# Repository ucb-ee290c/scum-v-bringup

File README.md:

# scum-v-bringup

Various files for bringing up the Single-Chip Micro Mote V (SCμM-V)

## Documentation

📖 **[SCuM-V Documentation (Nextra Site)](https://ucb-ee290c.github.io/scum-v-bringup/)** - Interactive documentation

### Contributing to Documentation
- **Nextra Documentation**: Edit files in `docs/` and submit pull requests
- **Legacy AsciiDoc**: See [Contributing to the specification document](docs/README.md)

### Installing Node.js and npm

npm is bundled with Node.js. Install Node.js for your OS, then verify with `node -v` and `npm -v`.

- **Windows**:
  - Download the LTS installer from the [official Node.js download page](https://nodejs.org/en/download/)
  - Run the `.msi` and follow the prompts
  - Verify: `node -v` and `npm -v`

- **macOS**:
  - Install Homebrew (if not installed):
    ```bash
    /bin/bash -c "$(curl -fsSL https://raw.githubusercontent.com/Homebrew/install/HEAD/install.sh)"
    ```
  - Install Node.js (includes npm):
    ```bash
    brew install node
    ```
  - Verify: `node -v` and `npm -v`

- **Linux (Ubuntu/Debian)**:
  - Update and install:
    ```bash
    sudo apt update
    sudo apt install nodejs npm
    ```
  - Verify: `node -v` and `npm -v`

- **More options**: See the official npm guide: [Downloading and installing Node.js and npm](https://docs.npmjs.com/downloading-and-installing-node-js-and-npm)

#### How to contribute to the docs
1. Fork the repo on GitHub: [ucb-ee290c/scum-v-bringup](https://github.com/ucb-ee290c/scum-v-bringup)
2. Clone your fork:
   ```bash
   git clone https://github.com/<your-username>/scum-v-bringup.git
   cd scum-v-bringup
   ```
3. Create a branch:
   ```bash
   git checkout -b docs/your-change
   ```
4. Edit files under `docs/`, preview locally (below), commit and push:
   ```bash
   git add .
   git commit -m "docs: describe your change"
   git push origin docs/your-change
   ```
5. Open a Pull Request to `ucb-ee290c/scum-v-bringup` with a clear description.

### Building Documentation Locally
```bash
cd docs
npm install
npm run dev    # Development server at http://localhost:3000
npm run build  # Production build
```

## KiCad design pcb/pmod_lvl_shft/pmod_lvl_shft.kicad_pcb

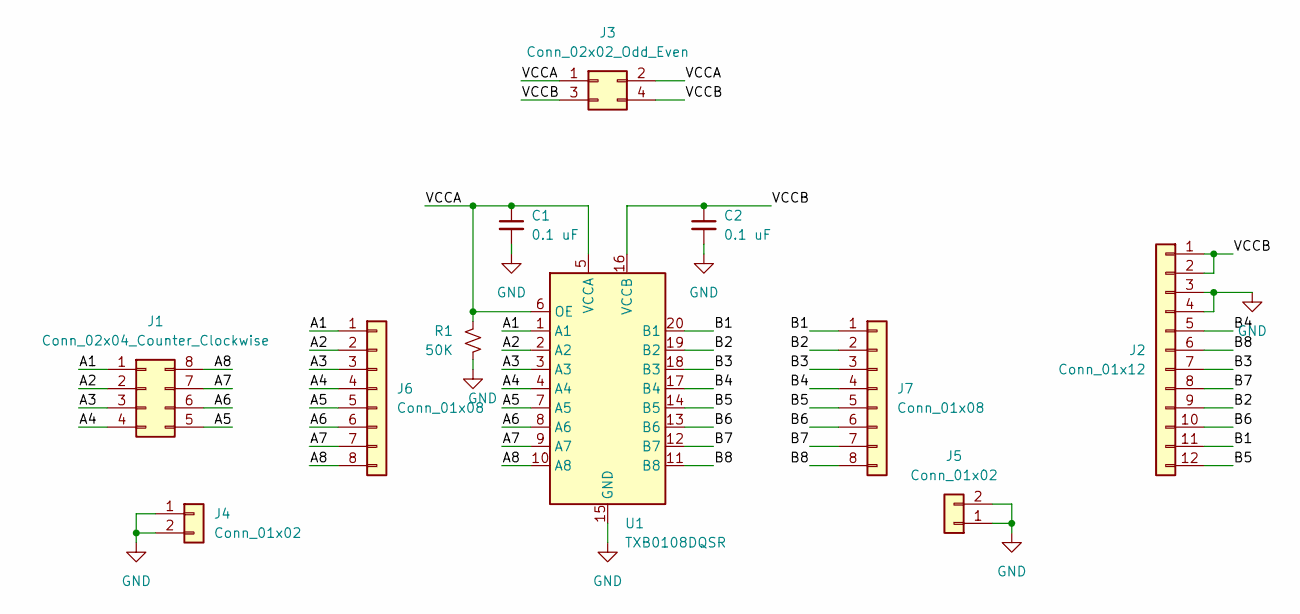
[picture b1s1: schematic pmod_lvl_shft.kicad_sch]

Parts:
C1, C2: 0.1 uF; C_0603_1608Metric
J1: Conn_02x04_Counter_Clockwise; PinHeader_2x04_P2.54mm_Vertical
J2: Conn_01x12; PinHeader_2x06_P2.54mm_Horizontal
J3: Conn_02x02_Odd_Even; PinHeader_2x02_P2.54mm_Vertical
J4, J5: Conn_01x02; PinHeader_1x02_P2.54mm_Vertical
J6, J7: Conn_01x08; PinHeader_1x08_P2.54mm_Vertical
R1: 50K; R_0603_1608Metric
U1: TXB0108DQSR; USON-20_2x4mm_P0.4mm

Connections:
/A1: J1.1, J6.1, U1.1 (A1)
/A2: J1.2, J6.2, U1.2 (A2)
/A3: J1.3, J6.3, U1.3 (A3)
/A4: J1.4, J6.4, U1.4 (A4)
/A5: J1.5, J6.5, U1.7 (A5)
/A6: J1.6, J6.6, U1.8 (A6)
/A7: J1.7, J6.7, U1.9 (A7)
/A8: J1.8, J6.8, U1.10 (A8)
/B1: J2.11, J7.1, U1.20 (B1)
/B2: J2.9, J7.2, U1.19 (B2)
/B3: J2.7, J7.3, U1.18 (B3)
/B4: J2.5, J7.4, U1.17 (B4)
/B5: J2.12, J7.5, U1.14 (B5)
/B6: J2.10, J7.6, U1.13 (B6)
/B7: J2.8, J7.7, U1.12 (B7)
/B8: J2.6, J7.8, U1.11 (B8)
/VCCA: C1.1, J3.1, J3.2, R1.1, U1.5 (VCCA), U1.6 (OE)
/VCCB: C2.1, J2.1, J2.2, J3.3, J3.4, U1.16 (VCCB)
GND: C1.2, C2.2, J2.3, J2.4, J4.1, J4.2, J5.1, J5.2, R1.2, U1.15 (GND)

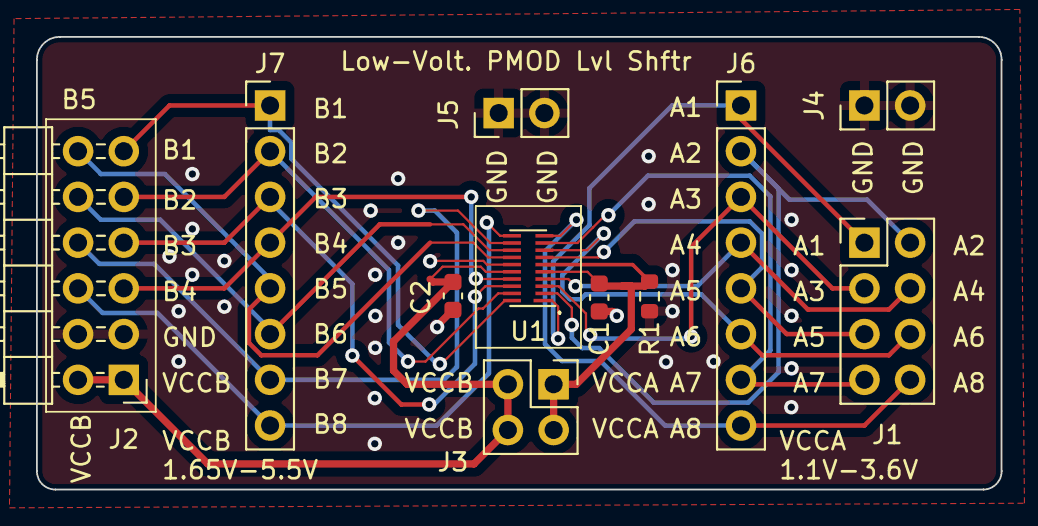
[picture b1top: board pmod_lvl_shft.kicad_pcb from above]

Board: 2 copper layers, 53.6 x 25.1 mm, 11 parts (0 on the bottom side), 19 nets.

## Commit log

2022-12-06 init
2022-12-06 add scan chain wip
2023-01-05 simulation verified UART<->scan chain bridge
2023-01-05 readme
2023-02-07 SCAN_CLK_FREQ fixed, set to 1 kHz, redefined UART response
2023-02-07 Added wip Python client to communicate with FPGA
2023-02-07 Vivado proj tcl (build.tcl), .gitignore, and build checkpoint
2023-02-11 ASC client packets to bypass on-chip clocks
2023-02-11 More README documentation on hardware setup
2023-02-11 Abstractions of scan chain payloads
2023-02-11 FPGA setup and bitstream generation documentation
2023-02-11 Fixes to and renaming of build.tcl -> create_project.tcl
2023-02-11 Added README section on writing to the ASC
2023-02-12 Add ability to use button 0 for chip reset
2023-02-19 add scanchain payload class and analog_rf payload
2023-02-19 Added scum_firmware
2023-02-19 Simple hello world firmware + fixes
2023-02-19 Added tl_host.py
2023-02-19 Added TileLinkTrafficAdapter-F446
2023-02-26 Adding documentation on the TSI setup with STM32
2023-02-26 Added tiny_adapter and proxyFESVR fork
2023-02-26 Added project structure to README
2023-02-26 ASC bitstream flashing guide and Tcl script fix/guide
2023-02-26 Remove sim_compile_state
2023-03-21 Working scum-v bootload
    64-bit oriented TSI interface uploads 8 bytes to SRAM at a time in double-word aligned addressing
2023-04-08 Added code from FPU experiments
2023-04-08 Cleanup of scan chain client.py
2023-04-26 Implemented SCuM-V22 baseband C library
2023-04-26 SRAM poke to verify bootload completion
2023-04-26 ADC clock tuning in the scan chain
2023-04-26 Include baseband library in Makefile
2023-04-26 Added BLE and LRWPAN loopback tests
2023-04-26 scum_firmware setup for dynamic power consumption test
2023-04-26 ARCH and ABI compiler flags for SCuM-V23
2023-04-28 Add oscibear rx sim
2023-05-23 Added MMCM clock generation wizard
2023-05-23 Added 200 kHz and 20 MHz generated CPU clocks
2023-08-18 scumv-23 spec doc, asciidoc setup & guide
2023-08-18 Create publish.yml GH action
2023-08-18 Handle vscode vs gh actions envs for spec doc
2023-08-18 More spec doc substance
2023-08-18 Power system and uv-adc specs
2023-08-22 Documenting the digital core
2023-08-22 Rename ebook.pdf to SCuM-V23.pdf
2023-08-22 Add links to the documentation
2023-08-22 Use SCuM-V23.pdf link
2023-08-22 Add workarounds around asciidoctor ghpages action
2023-08-23 More documentation throughout
2023-08-24 added RF Analog section
2023-08-24 Include radio.adoc in scum-v23.adoc
2023-08-29 Change radar to radar transmitter
2023-08-31 Update SCuM-V23.adoc
    Names on tasks
2023-08-31 Add designer, author, and bringup names
2023-08-31 Format names
2023-08-31 Update SCuM-V23.adoc
    point final review slides to bringup drive
2023-08-31 point final review to bringup drive
2023-09-01 Revert "Format names"
    This reverts commit 35be374bae99f2b7b4f217b85905e1dc431e396a.
2023-09-01 Revert "Add designer, author, and bringup names"
    This reverts commit bd3a76473c84f6a26f82226a87aa97f5dfc6dda7.
2023-09-02 Fix google slides links
2023-09-02 Edit DRI names for documentation
2023-09-02 Add radar documentation
2023-09-02 Convert PDF images to PNG images
2023-09-02 Add radar layout
2023-09-02 Add documentation for radio transmitter
2023-09-05 Add files for encryption modules documentation
2023-09-05 Add base address for Scumvtuning
2023-10-05 Format register table for radars
2023-10-05 Update ramp generator clock mux select
2023-12-03 tl_host for 32-bit targets
2023-12-06 Change V22 to V23
2023-12-06 Fix UART base address in scum.h
2023-12-06 Use different baudrate, worked with 200 kHz
2023-12-08 Read 16 bytes from serial
2023-12-08 Lint tl_host.py
2023-12-08 Add TileLink adapter firmware for STM32H723ZGT6
2023-12-08 Change MISO -> OUT and MOSI -> IN in H723 firmware
2023-12-09 Change from 64-bit data to 32-bit data
2023-12-13 Revert "Change from 64-bit data to 32-bit data"
    This reverts commit 6d54f9f602f0e73b2d929a87955d22fd9ce4ed78.
2023-12-17 Update scum_firmware source from scum-sim-par
2023-12-17 Added scripts/smartelf2hex.sh
2023-12-17 Add template project
2023-12-17 Poll TL_CLK instead of an interrupt
2023-12-19 Increase CPU clock to 500 MHz / HCLK to 250 MHz
2023-12-19 Poll TL_CLK instead of an interrupt (#4)
    * Poll TL_CLK instead of an interrupt
    * Increase CPU clock to 500 MHz / HCLK to 250 MHz
2023-12-19 Clean up TL host script
2023-12-19 Add information about STM32H723ZG to README.md
2024-01-05 Add sensor_adc python test script
2024-01-08 Clarify base address of uv-adc in docs
2024-01-08 Add example usage doc to sensor_adc.py
2024-01-09 sensor_adc.py more comprehensive test script, option for bootload, better config function
2024-01-09 Added sensor_adc signal processing scripts; mainly SENSOR_OUT related
    Associated raw data (csv)
    https://berkeley.box.com/s/r1d8qseaqz2fsj55ihhmtkpoj31uxdyu
2024-01-22 Add sensor_adc_test firmware
2024-01-30 Remove scanchain.gen files
2024-01-30 Update the README.md with how to create the Vivado project
2024-02-02 Remove clock generation from FPGA
2024-02-02 Ignore steps to reproduce files
2024-02-02 Clean up FPGA client script
2024-02-02 Add SCuM-V23 scanchain Verilog file
2024-02-03 Update FPGA code and client script to match SCuM-V23's scan chain
2024-02-05 WIP BLE & 15.4 loopback firmware changes
2024-02-05 sensor_adc_test firmware with log_counters data collection
2024-02-05 Scan chain VCO LO tuning/characterization script
2024-02-08 Fix typo in client.py
2024-02-09 Fix order of oscillator scan chain registers
2024-02-22 Updated more sensor ADC test firmware
2024-02-22 Add plotting scripts and logs for ADC counter tests
2024-03-05 4 instructions per sensor_adc_test logging cycle
2024-03-06 comment out kick IDAC to start up, and set default idac val to be 16
2024-03-10 Sensor ADC tests at 100M/25M CPU/ADC
2024-03-10 Added parse_counter_logs script and data for other CPU/ADC ratios
2024-04-24 Updated parse_counter_logs
2024-05-23 Work in progress sensoradc-bringup FPGA code
2024-05-23 Pruning and bufg clock buffers for ADC_CLOCK
2024-05-23 sensoradc-bringup clock_gen, dechopper, sensor_out_fsm
2024-05-23 Constraints tweak, track design checkpoint
2024-05-23 WIP scumv22 scanchain redux
2024-05-27 create_project.tcl -> make_proj.tcl
2024-05-27 sensoradc-bringup FPGA updated constraints and design checkpoint
2024-05-28 Remove CPU_CLK preventing scan chain synth
2024-05-28 More progress on sensoradc-bringup
2024-05-29 sensoradc-bringup data_translator, uart connection, timing closure
2024-05-29 Fix bugs in a7top
2024-05-29 Add uart_decode.py
2024-05-30 Latest verilog and python
2024-07-16 Successful SCuM-V23B boot
    Working boot with python tl_host --target power_test
2024-07-16 ble_loopback revisions, alignment with scum-v24, not working
2024-07-30 Update README.md with xpack toolchain
2024-07-31 Add sysverilog-source files for R=32,000
2024-07-31 fix: update verilog modules to match sysverilog modules
2024-07-31 Remove unneeded, unused files
2024-07-31 fix: update Verilog modules to match SystemVerilog definitions and fix syntax issues
2024-08-01 feat: reimplement decimator_tb for compatibility with Xilinx Vivado by replacing integer with reg arrays
2024-08-01 Several fixes to comb, dsp_clock_domain_wrapper, integrators for R=32,000 update
2024-08-01 Add PMOD level shfiter PCB
2024-08-01 Build .adoc Files for GitHub Pages from 93667d8c255ccafe95bf72764eb72e34916c16d5
2024-08-01 Docs update for scum-v24
2024-09-07 sensor_adc_test demo with delayed startup, clock divider synchronization
    To eliminate delay between chopper clock edges, for test
2024-09-07 Changes for successful testing session
    Still having harmonics issues
2025-07-27 Copy over scum-test-tools BSP from scumv25 repo
2025-07-27 Copy lib/htif from scum-test-tools scumv25
2025-07-27 scum-test-tools scumv25 startup.S, Makefile, firmware.map
2025-07-27 Copy scum-test-tools core/src from scumv25
2025-07-28 Working compilation for scumv25 (rv64 & new MMIO map)
2025-07-29 Make necessary changed for rv64 -> rv32 for scumv24b
2025-07-29 Correct scumv24 baseband int map
    Source diagram made
2025-07-30 Single TL packet working SCuM-V24B
2025-07-30 Seemingly working single-shot TL transactions
2025-07-31 Initial implementation of scumv-controller FPGA SerialTL
2025-07-31 Somewhat working UART<->TL traffic adapter
2025-08-04 scumv-controller add IO pins to XDC for TL bus
2025-08-04 Revisions to scumv-controller FSMs per benchtop debugging with ILA
2025-08-05 Working scumv-controller single TL sends on bench
2025-08-05 Improved scumv-controller TB with TL inspector
2025-08-05 some progress
    FIFOs causing trouble
2025-08-05 Some simplification of FSM
2025-08-05 Redesigned uart handler and stl uart client FSMs
2025-08-06 Update design spec
2025-08-06 Several fixes to scumv-controller allowing successful boot
2025-08-13 Remove ILA from scumv-controller a7top
2025-08-13 Correct status0 register concatenation order in firmware
2025-08-13 SCuM-V can reliable SerialTL boot with CPU clock = 1 MHz
2025-08-13 Add back HAL_UART_finishTX(UART0) - needs to be tested
2025-08-13 fix typo lol
2025-08-16 ble_loopback -> LO sweep via CT LUTs
2025-08-16 Update DESIGN_SPEC
2025-08-16 2Mbaud UART in scumv-controller, more comprehensive TB
2025-08-16 Update tl_host_sim.py for longer test vectors/stress test
2025-08-16 Fix compilation errors on newer xpack compiler
2025-08-16 Force add simulation test vectors binaries
2025-08-16 Remove outdated tiny_adapter
2025-08-16 Update documentation
2025-08-16 Update README, remove proxyFESVR
2025-08-18 Some improvements to scum-v controller TB
2025-08-18 Add sim testbench waveform config to scumv-controller proj
2025-08-18 Increase FIFO size in scumvcontroller_uart_handler
2025-08-18 Build .adoc Files for GitHub Pages from f6521d681fd6c391395ce10d9a6dff2793f00de0
2025-08-18 Add WIP testbench and uart passthrough
2025-08-18 scumv-controller TBs, fix CDCs & timing, ble_loopback for sim
2025-08-18 Some attempted debugging of finnicky delay
2025-08-18 Fix async clock groups in XDC
2025-08-18 Remove single integration tb
2025-08-18 Update XPR
2025-08-18 Update wcfg
2025-08-19 Little bit of progress
2025-08-19 Documentation, loopback tweaks
2025-08-20 Bug fixes to title/style
2025-08-20 Better styling
2025-08-20 Some better Nextra components usage
2025-08-21 Improvement to digital-baseband docs
2025-08-21 Remove old docs/ directory, replace with docs-nextra/
2025-08-21 Implement github workflow for nextra
2025-08-21 Remove troublesome Icon.tsx
2025-08-21 Documentation workflow master->main
2025-08-21 Fix 2nd reference master->main
2025-08-21 deploy: daf70329869c46acaabbdebc198bc10a487f2baf
2025-08-25 Improvements to documentation
2025-08-25 deploy: a0552e2c41d6e630ffd576ee33b6cdcabc970147
2025-08-25 deploy: e7951362df601e2f66bf7724cb88be83fe6bd0fc
2025-08-25 add PCB layout image
2025-08-25 deploy: 40037ea914274f4b6246ef25ed030ae01b009227
2025-09-04 Up the tl_host.py baudrate to match FPGA
2025-09-04 deploy: 7a908dcb0ba0eb0cf8458ba3b5b37d9db074506f
2025-09-09 adding riscv installation instructions for macOS with fix for ./configure
2025-09-09 removing {} commands
2025-09-09 Add docs contribution guide
2025-09-09 Changed to firmware-development.mdx
2025-09-09 deploy: 3358c728fdb02f49a1b62ca72dbdd766fa7574e6
2025-09-11 Improve tl_host UART interface w/o firmware in loop
2025-09-11 deploy: b6302120c40f10854f53b84afcde32c334771c18
2025-09-11 Add missing Steps import
2025-09-11 deploy: 379e8dab9177dd433e81670c17089aac4655ee24
2025-09-19 Update scumvtuning regmap, add scumv_tuning clock sweep via tl_host
2025-09-19 deploy: b5b3c5a586dba6dc2fe78ce4d4ad4934caa05c87
2025-09-19 Add helper methods for SerialTL MMIO access
2025-09-19 deploy: 8ae2b0bef37aeb1b8c0e3c735d228267abfe820f
2025-09-29 Add baseband.py for lo sweep test
2025-09-29 deploy: d244dbdfcf63b9e05846d27a8e5518d756c91f0c
2025-10-03 Add ct_sweep_both to sw/baseband.py
2025-10-03 deploy: ba045247ef62d4a019205130627d7a6fb37f5f01
2025-10-06 Clean up lrwpan_loopback demo
2025-10-06 deploy: ba2259502c2ac5e71e5ed3bbea82baff0f725dbe
2025-10-09 Update power system documentation
2025-10-09 deploy: 05fe998dac37050c25d2608e1a20e6a800aef042
